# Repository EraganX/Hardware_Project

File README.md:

# First Year Hardware Project
Component - LCD , Button , PowerSuply <br/>
Proteus and Atmel studio files included.

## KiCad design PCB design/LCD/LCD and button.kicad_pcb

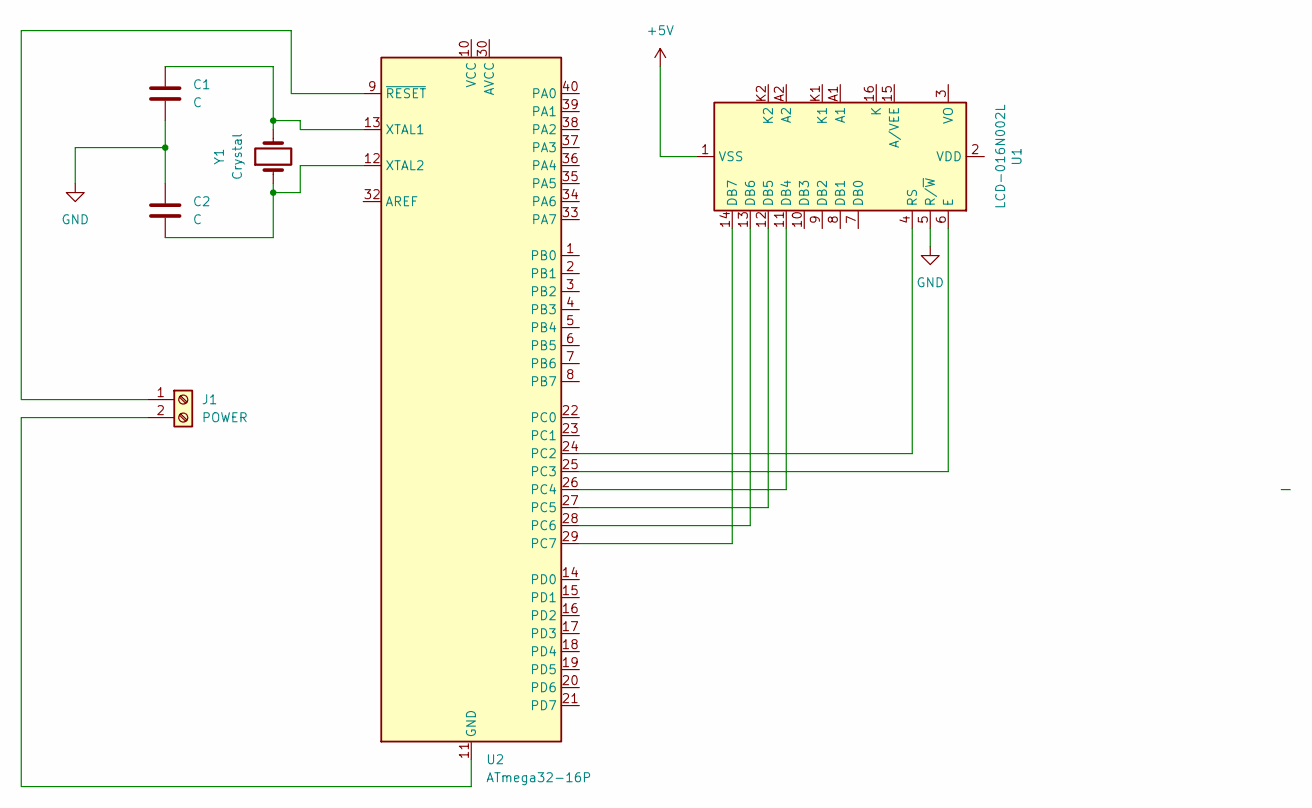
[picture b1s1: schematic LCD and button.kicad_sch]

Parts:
C1, C2: C; CP_Elec_3x5.3
J1: POWER; TerminalBlock_RND_205-00045_1x02_P5.00mm_Horizontal
U1: LCD-016N002L
U2: ATmega32-16P; DIP-40_W15.24mm
Y1: Crystal; Crystal_SMD_3215-2Pin_3.2x1.5mm

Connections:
GND: C1.2, C2.1, U1.5 (R/~W)
unnamed: C1.1, U2.13 (XTAL1), Y1.2
unnamed: C2.2, U2.12 (XTAL2), Y1.1
unnamed: J1.1, U2.9 (~RESET)
unnamed: J1.2, U2.11 (GND), U2.31 (GND)
unnamed: U1.4 (RS), U2.24 (PC2)
unnamed: U1.6 (E), U2.25 (PC3)
unnamed: U1.11 (DB4), U2.26 (PC4)
unnamed: U1.12 (DB5), U2.27 (PC5)
unnamed: U1.13 (DB6), U2.28 (PC6)
unnamed: U1.14 (DB7), U2.29 (PC7)

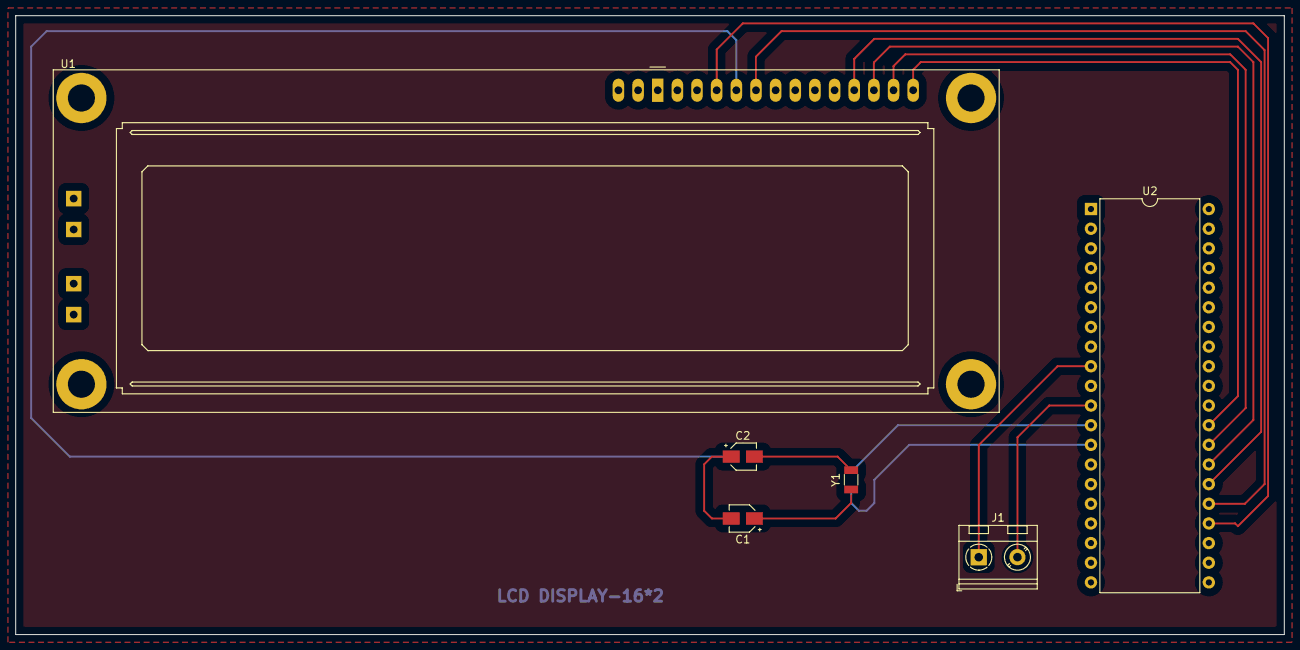
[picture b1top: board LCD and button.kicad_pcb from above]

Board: 2 copper layers, 164.0 x 80.0 mm, 6 parts (0 on the bottom side), 11 nets.

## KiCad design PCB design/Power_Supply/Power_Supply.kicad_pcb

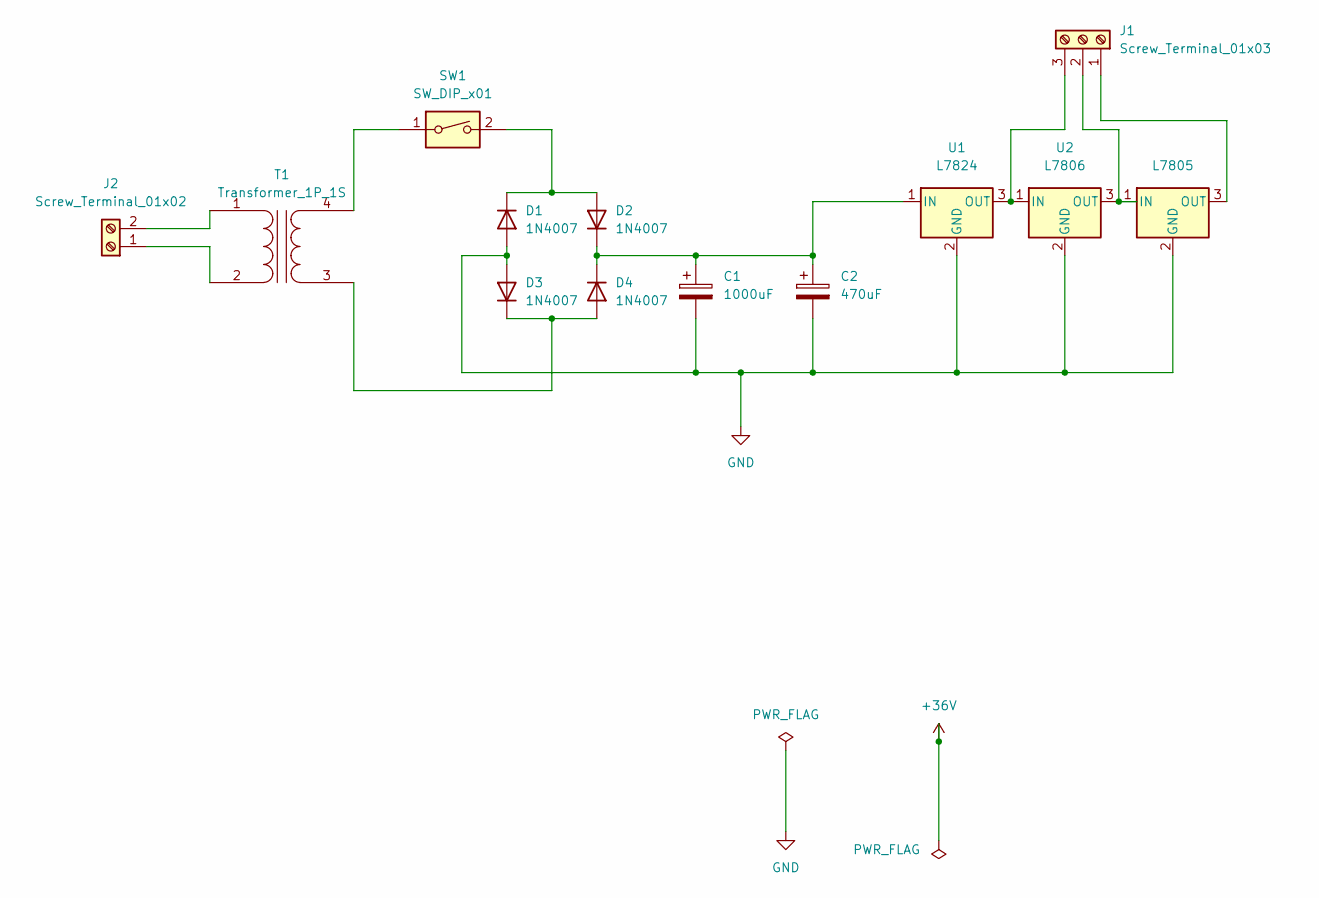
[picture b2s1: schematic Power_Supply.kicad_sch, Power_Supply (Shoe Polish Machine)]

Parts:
C1: 1000uF; CP_Radial_D10.0mm_P5.00mm
C2: 470uF; CP_Radial_D10.0mm_P5.00mm
D1, D2, D3, D4: 1N4007; D_DO-41_SOD81_P10.16mm_Horizontal
J1: Screw_Terminal_01x03; TerminalBlock_MetzConnect_Type086_RT03403HBLC_1x03_P3.81mm_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
J2: Screw_Terminal_01x02; TerminalBlock_RND_205-00298_1x02_P10.00mm_Horizontal
SW1: SW_DIP_x01; SW_E-Switch_EG1224_SPDT_Angled
T1: Transformer_1P_1S; Transformer_NF_ETAL_1-1_P1200
U1: L7824; TO-220-3_Vertical
U2: L7806; TO-220F-3_Vertical
U3: L7805; TO-220F-3_Vertical

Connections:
GND: C1.2, C2.2, D1.2 (A), D3.2 (A), U1.2 (GND), U2.2 (GND), U3.2 (GND)
unnamed: C1.1, C2.1, D2.1 (K), D4.1 (K), U1.1 (IN)
unnamed: D1.1 (K), D2.2 (A), SW1.2
unnamed: D3.1 (K), D4.2 (A), T1.3 (SA)
unnamed: J1.1, U3.3 (OUT)
unnamed: J1.2, U2.3 (OUT), U3.1 (IN)
unnamed: J1.3, U1.3 (OUT), U2.1 (IN)
unnamed: J2.1, T1.2 (AB)
unnamed: J2.2, T1.1 (AA)
unnamed: SW1.1, T1.4 (SB)

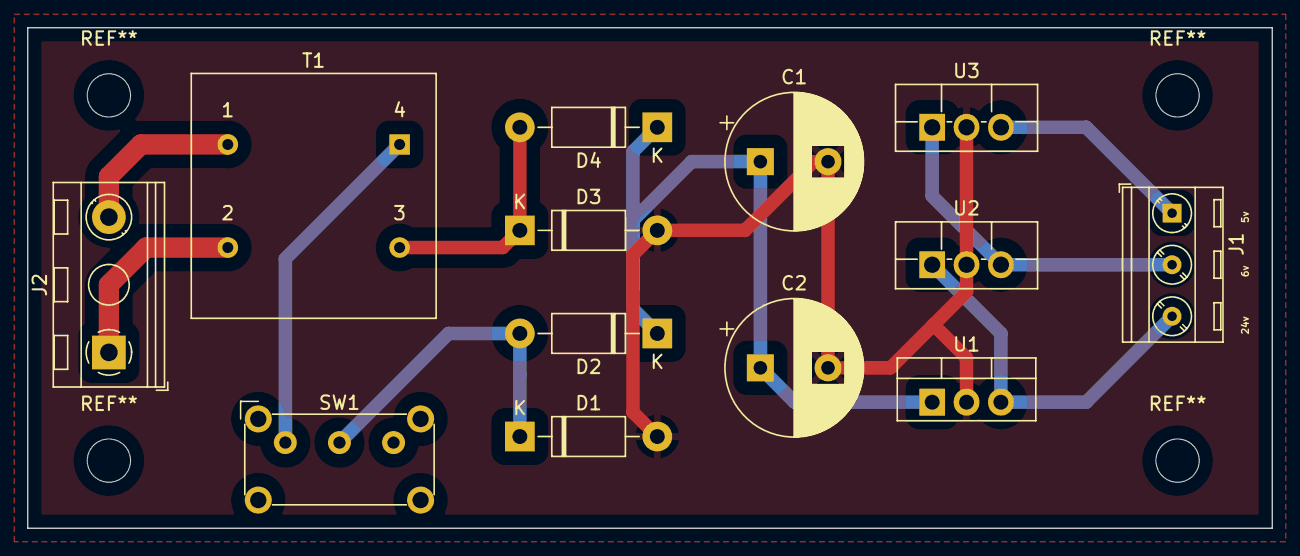
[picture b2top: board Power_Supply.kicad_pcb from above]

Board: 2 copper layers, 92.0 x 37.0 mm, 13 parts (0 on the bottom side), 10 nets.

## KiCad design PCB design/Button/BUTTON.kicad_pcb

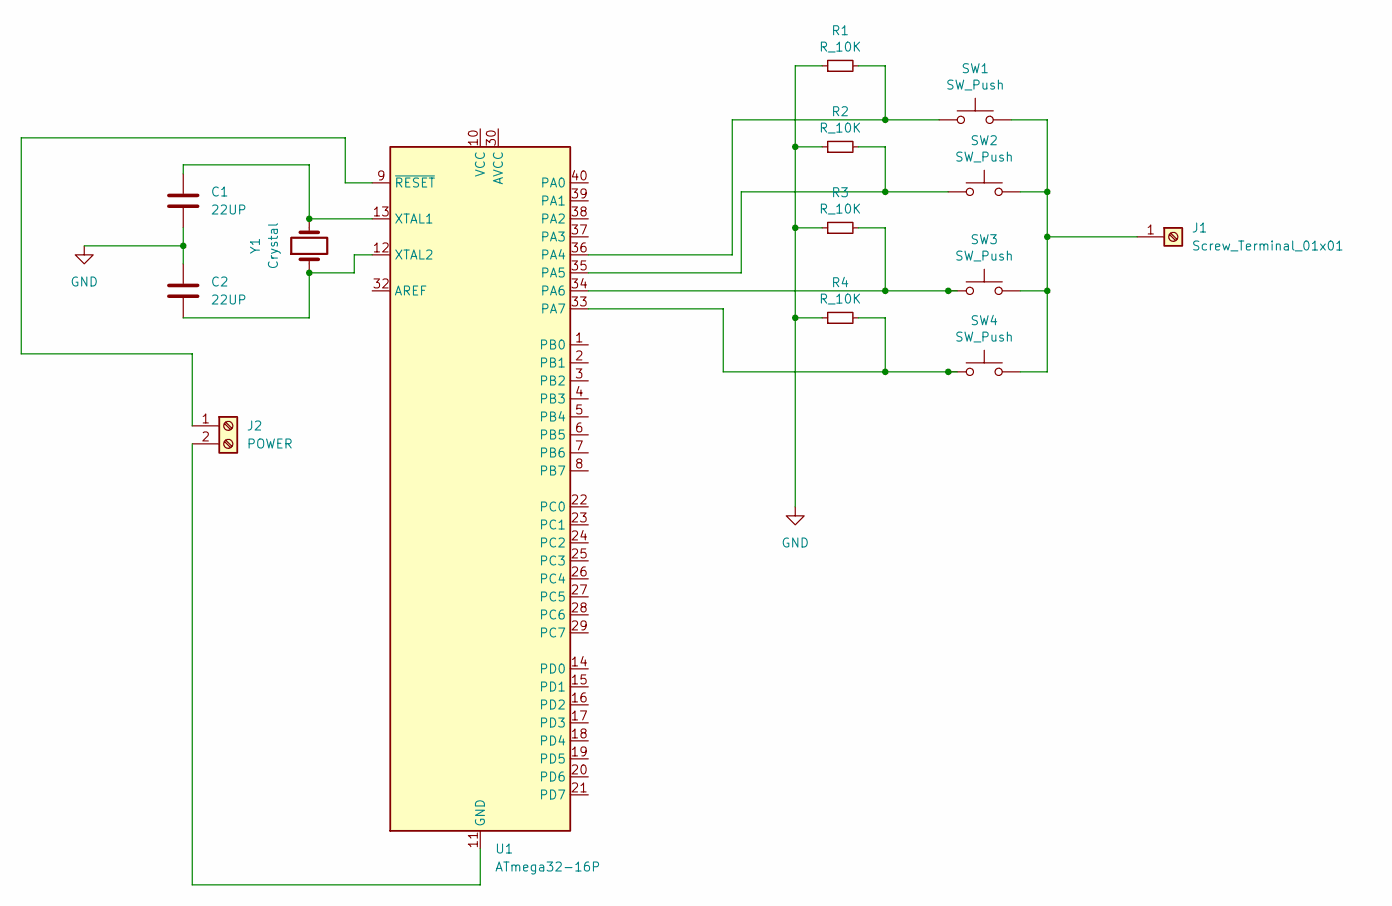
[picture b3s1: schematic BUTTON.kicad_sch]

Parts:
C1, C2: 22UP; CP_Elec_3x5.3
J1: Screw_Terminal_01x01; TerminalBlock_MetzConnect_360271_1x01_Horizontal_ScrewM3.0_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
J2: POWER; TerminalBlock_RND_205-00045_1x02_P5.00mm_Horizontal
R1, R2, R3, R4: R_10K; R_0805_2012Metric
SW1, SW2, SW3, SW4: SW_Push; SW_PUSH_6mm
U1: ATmega32-16P; DIP-40_W15.24mm
Y1: Crystal; Crystal_SMD_3215-2Pin_3.2x1.5mm

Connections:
GND: C1.2, C2.1, R1.1, R2.1, R3.1, R4.1
unnamed: C1.1, U1.13 (XTAL1), Y1.2
unnamed: C2.2, U1.12 (XTAL2), Y1.1
unnamed: J1.1, SW1.2, SW2.2, SW3.2, SW4.2
unnamed: J2.1, U1.9 (~RESET)
unnamed: J2.2, U1.11 (GND), U1.31 (GND)
unnamed: R1.2, SW1.1, U1.36 (PA4)
unnamed: R2.2, SW2.1, U1.35 (PA5)
unnamed: R3.2, SW3.1, U1.34 (PA6)
unnamed: R4.2, SW4.1, U1.33 (PA7)

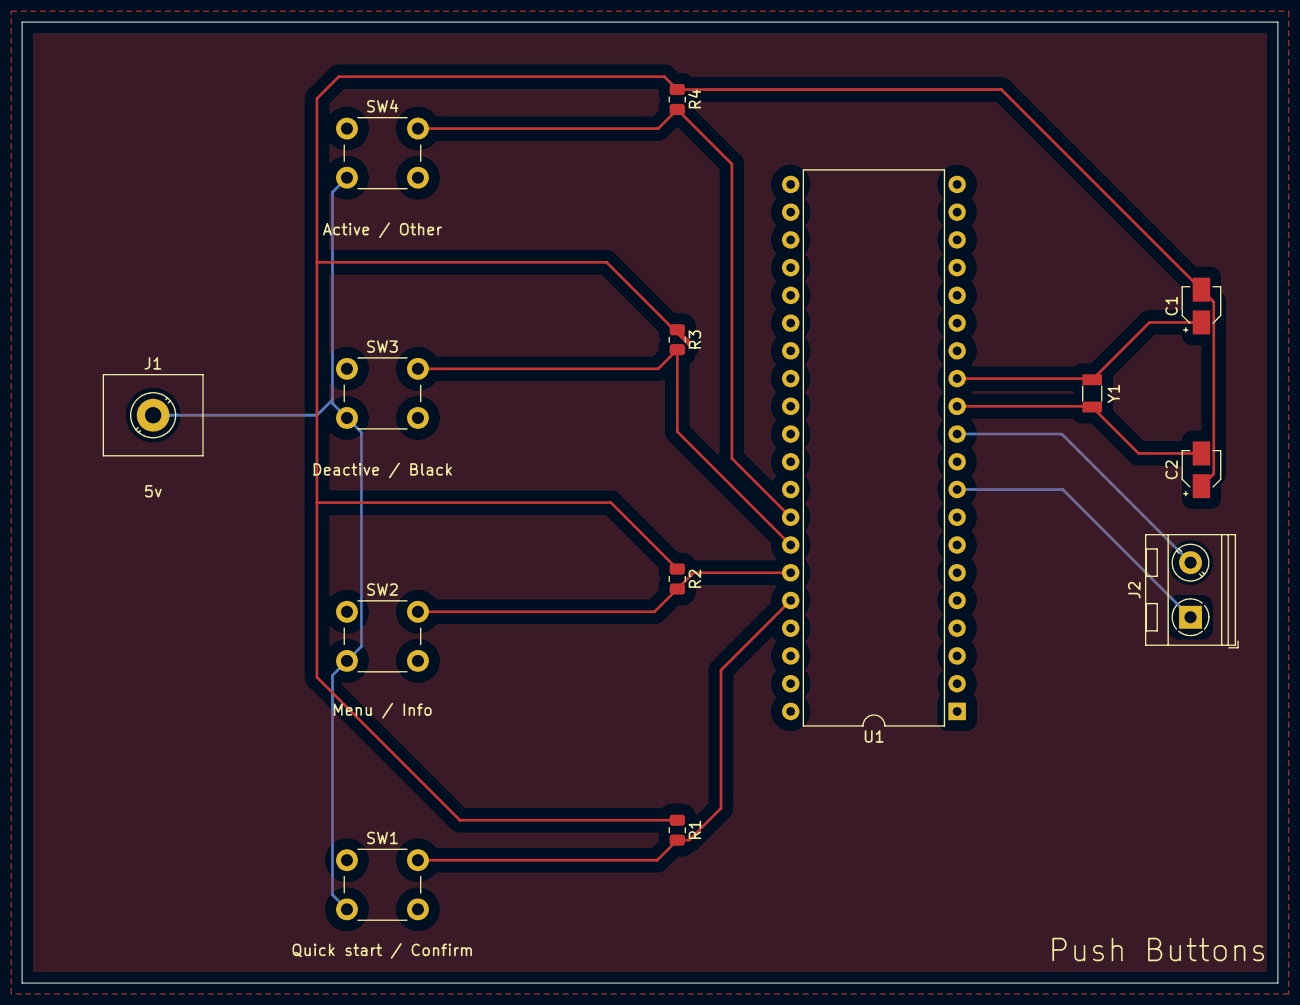
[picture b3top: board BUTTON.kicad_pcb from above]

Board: 2 copper layers, 115.0 x 88.0 mm, 14 parts (0 on the bottom side), 10 nets.

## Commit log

2022-05-02 LCD and Button Upload
    LCD and Botton. need to fix some changes.
2022-05-14 Code collection
    LCD, Button, Ultrasonic, IR sensors, Fan
2022-05-21 test
2022-05-24 Final Code
    first-year hardware project final code with proteus simulation.
2022-06-09 PCB design
    PCB design using KiCad software. (LCD, Button, and Power supply)
2022-07-05 Screenshots
